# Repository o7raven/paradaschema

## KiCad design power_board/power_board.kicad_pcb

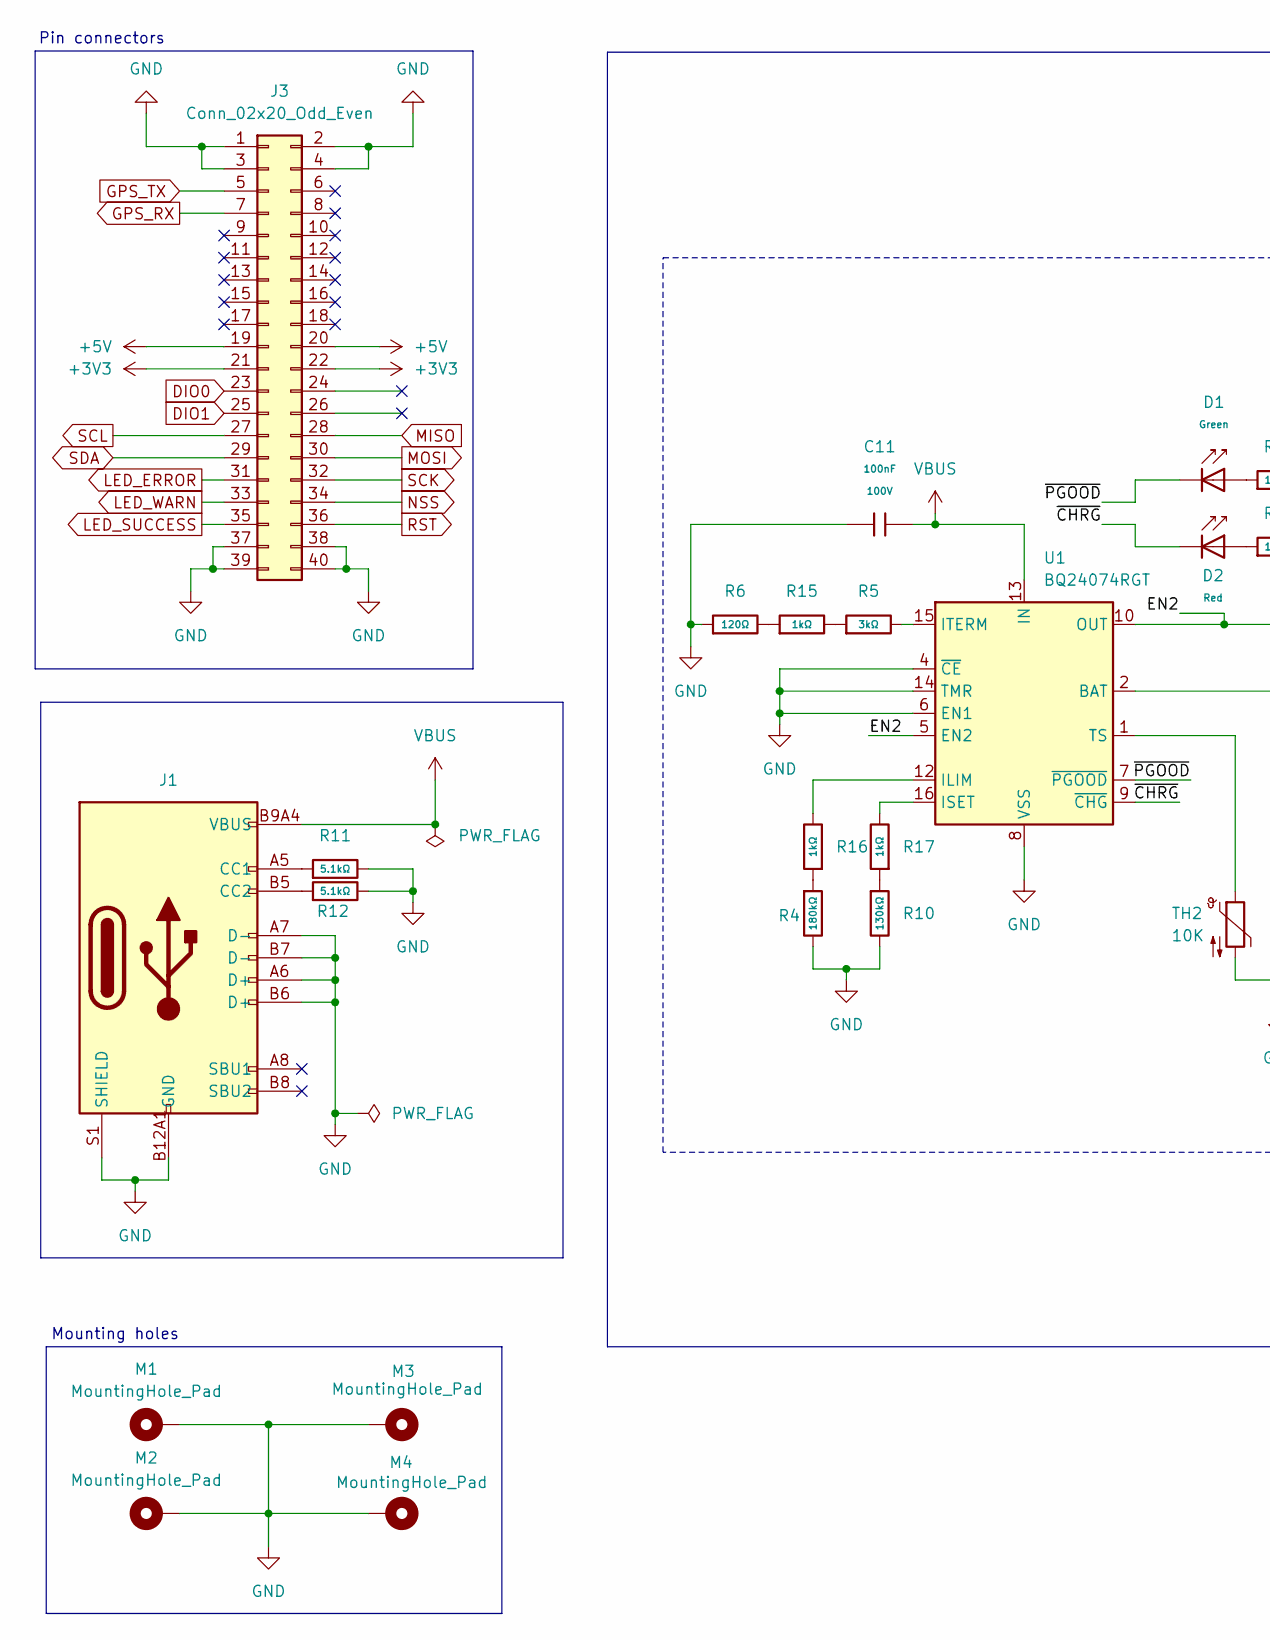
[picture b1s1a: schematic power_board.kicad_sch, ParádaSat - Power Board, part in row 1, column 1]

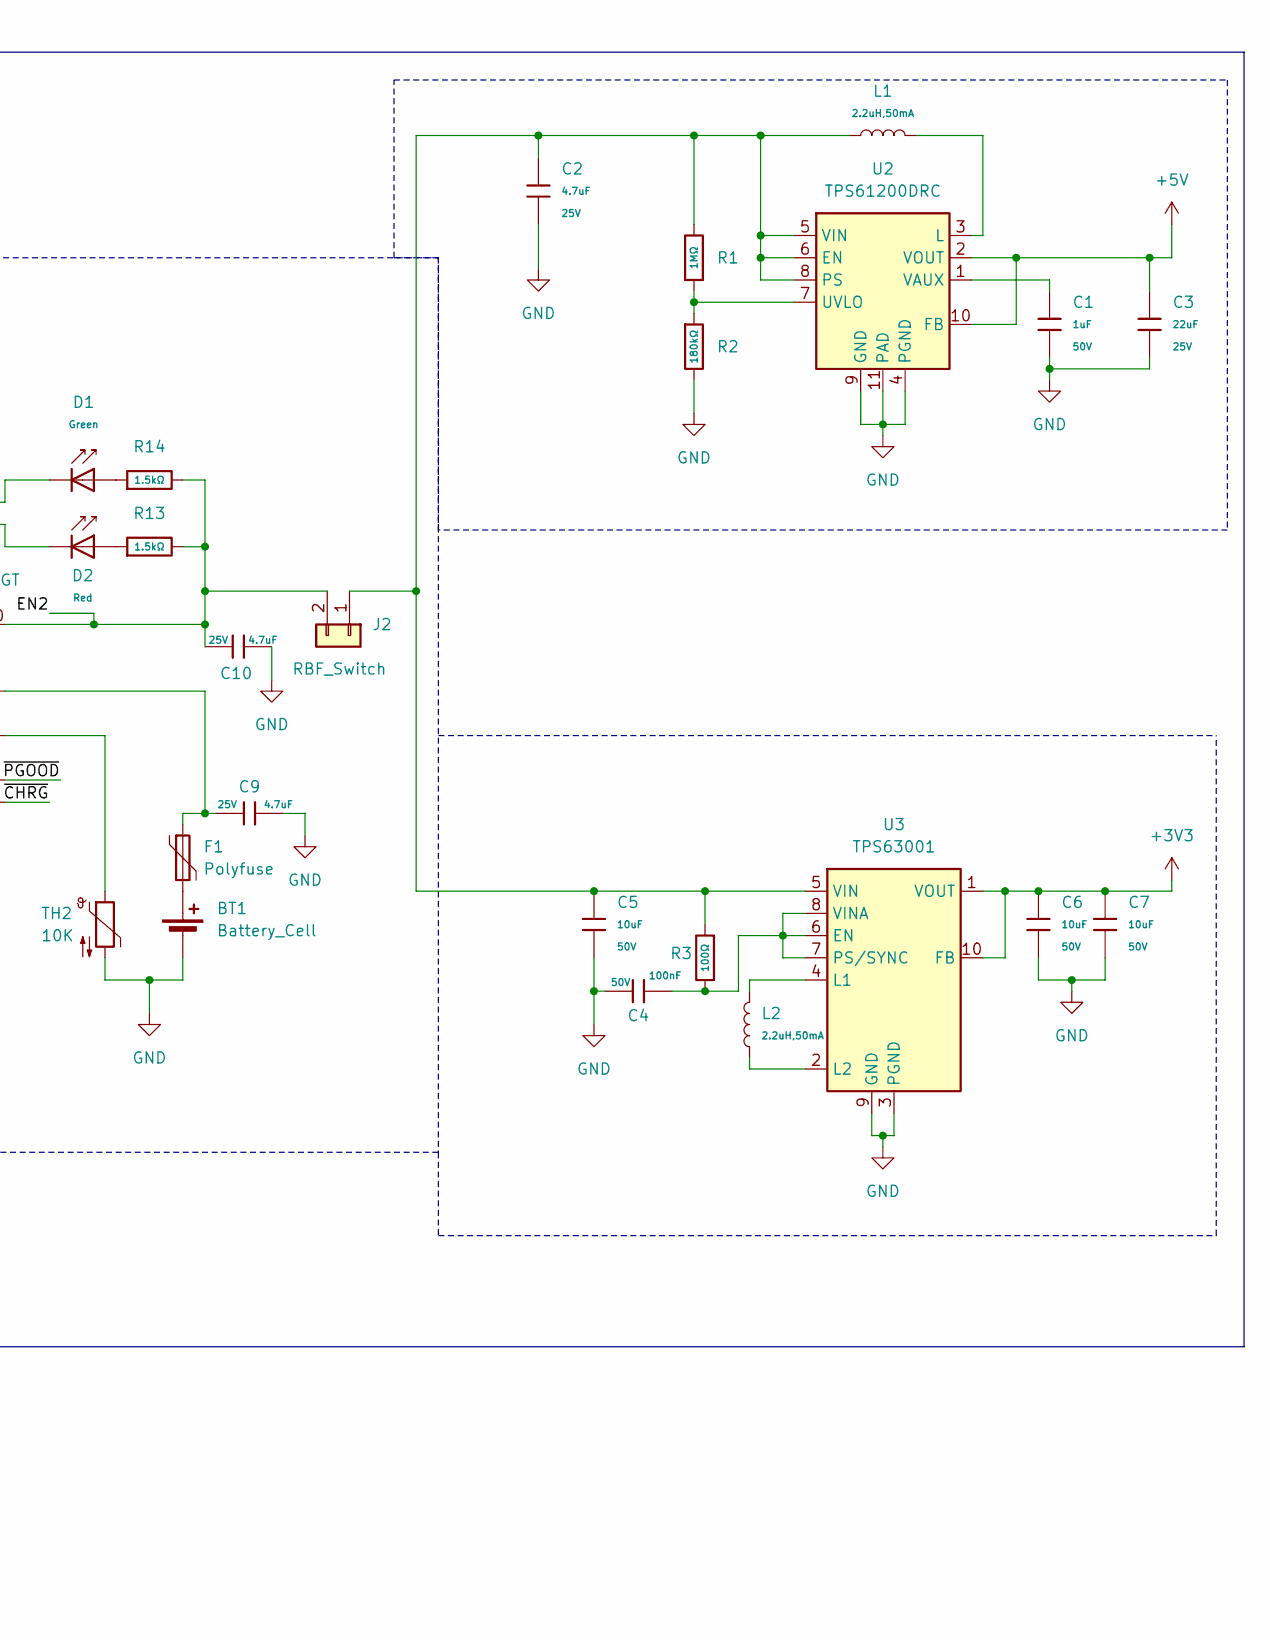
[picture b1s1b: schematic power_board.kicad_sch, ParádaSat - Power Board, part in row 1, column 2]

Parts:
BT1: Battery_Cell; BatteryHolder_MPD_BH-18650-PC
C1: 1uF; C_0805; Voltage Rated 50V; Tolerance ±10%; Part CL21B105KBFNNNE; LCSC C28323
C2, C9, C10: 4.7uF; C_0805; Voltage Rated 25V; Tolerance ±10%; Part CL21A475KAQNNNE; LCSC C1779
C3: 22uF; C_0805; Voltage Rated 25V; Tolerance ±20%; Part CL21A226MAQNNNE; LCSC C45783
C4: 100nF; C_1206; Voltage Rated 50V; Tolerance ±10%; Part CL31B104KBCNNNC; LCSC C24497
C5, C6, C7: 10uF; C_1206; Voltage Rated 50V; Tolerance ±10%; Part CL31A106KBHNNNE; LCSC C13585
C11: 100nF; C_0805; Voltage Rated 100V; Tolerance ±10%; Part CL21B104KCFNNNE; LCSC C28233
D1: Green; D_0805; Part KT-0805G; LCSC C2297
D2: Red; D_0805; Forward Voltage (VF) 1.6V~2.6V; Part NCD0805R1; LCSC C84256
F1: Polyfuse; Fuse_1812_4532Metric_Pad1.30x3.40mm_HandSolder
J1: Connector, USB-TYPE-C-16P; TYPE-C-SMD_HX-TYPE-C-16PIN; LCSC C2927039
J2: RBF_Switch; PhoenixContact_MSTBA_2,5_2-G_1x02_P5.00mm_Horizontal
J3: Conn_02x20_Odd_Even; PinSocket_2x20_P2.54mm_Vertical
L1, L2: 2.2uH,50mA; L_0805; Tolerance ±10%; Part CMI201209U2R2KT; LCSC C1043
M1, M2, M3, M4: MountingHole_Pad; MountingHole_3.2mm_M3_DIN965_Pad
R1: 1MΩ; R_0805; Overload Voltage (Max) 150V; Tolerance ±1%; Part 0805W8F1004T5E; LCSC C17514
R2: 180kΩ; R_0805; Overload Voltage (Max) 150V; Tolerance ±1%; Part 0805W8F1803T5E; LCSC C17501
R3: 100Ω; R_1206; Overload Voltage (Max) 200V; Tolerance ±1%; Part 1206W4F1000T5E; LCSC C17901
R4: 180kΩ; R_0603; Overload Voltage (Max) 75V; Tolerance ±1%; Part 0603WAF1803T5E; LCSC C22827
R5: 3kΩ; R_0603; Overload Voltage (Max) 75V; Tolerance ±1%; Part 0603WAF3001T5E; LCSC C4211
R6: 120Ω; R_1206; Overload Voltage (Max) 200V; Tolerance ±1%; Part 1206W4F1200T5E; LCSC C17909
R10: 130kΩ; R_0603; Overload Voltage (Max) 75V; Tolerance ±1%; Part 0603WAF1303T5E; LCSC C22795
R11, R12: 5.1kΩ; R_0603; Overload Voltage (Max) 75V; Tolerance ±1%; Part 0603WAF5101T5E; LCSC C23186
R13, R14: 1.5kΩ; R_0805; Overload Voltage (Max) 150V; Tolerance ±1%; Part 0805W8F1501T5E; LCSC C4310
R15, R16, R17: 1kΩ; R_0603; Overload Voltage (Max) 75V; Tolerance ±1%; Part 0603WAF1001T5E; LCSC C21190
TH2: 10K; R_Axial_DIN0204_L3.6mm_D1.6mm_P2.54mm_Vertical
U1: BQ24074RGT; VQFN-16-1EP_3x3mm_P0.5mm_EP1.6x1.6mm
U2: TPS61200DRC; Texas_S-PVSON-N10_ThermalVias
U3: TPS63001; Texas_DRC0010J_ThermalVias

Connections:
+3V3: C6.1, C7.1, J3.21, J3.22, U3.1 (VOUT), U3.10 (FB)
+5V: C3.1, J3.19, J3.20, U2.2 (VOUT), U2.10 (FB)
/EN2: C10.1, J2.2, R13.2, R14.2, U1.5 (EN2), U1.10 (OUT), U1.11 (OUT)
/~CHRG: D2.1, U1.9 (~CHG)
/~PGOOD: D1.1, U1.7 (~PGOOD)
DIO0: J3.23
DIO1: J3.25
GND: BT1.2 (-), C1.2, C2.2, C3.2, C4.1, C5.2, C6.2, C7.2, C9.2, C10.2, C11.1, J1.A6 (D+), J1.A7 (D-), J1.A12B1 (GND), J1.B6 (D+), J1.B7 (D-), J1.B12A1 (GND), J1.S1 (SHIELD), J3.1, J3.2, J3.3, J3.4, J3.37, J3.38, J3.39, J3.40, M1.1 (1_1), M2.1 (1_1), M3.1 (1_1), M4.1 (1_1), R2.2, R4.2, R6.1, R10.2, R11.2, R12.2, TH2.2, U1.4 (~CE), U1.6 (EN1), U1.8 (VSS), U1.14 (TMR), U1.17 (VSS), U2.4 (PGND), U2.9 (GND), U2.11 (PAD), U3.3 (PGND), U3.9 (GND), U3.11 (PGND)
GPS_RX: J3.7
GPS_TX: J3.5
LED_ERROR: J3.31
LED_SUCCESS: J3.35
LED_WARN: J3.33
MISO: J3.28
MOSI: J3.30
NSS: J3.34
unnamed: BT1.1 (+), F1.2
unnamed: C9.1, F1.1, U1.2 (BAT), U1.3 (BAT)
unnamed: D1.2, R14.1
unnamed: D2.2, R13.1
unnamed: J1.A5 (CC1), R11.1
unnamed: J1.B5 (CC2), R12.1
unnamed: C2.1, C5.1, J2.1, L1.1, R1.2, R3.2, U2.5 (VIN), U2.6 (EN), U2.8 (PS), U3.5 (VIN)
unnamed: R10.1, R17.1
unnamed: R6.2, R15.1
unnamed: R5.1, R15.2
unnamed: R4.1, R16.1
unnamed: R16.2, U1.12 (ILIM)
unnamed: R17.2, U1.16 (ISET)
unnamed: R5.2, U1.15 (ITERM)
unnamed: TH2.1, U1.1 (TS)
unnamed: L1.2, U2.3 (L)
unnamed: R1.1, R2.1, U2.7 (UVLO)
unnamed: C1.1, U2.1 (VAUX)
unnamed: C4.2, R3.1, U3.6 (EN), U3.7 (PS/SYNC), U3.8 (VINA)
unnamed: L2.2, U3.4 (L1)
unnamed: L2.1, U3.2 (L2)
RST: J3.36
SCK: J3.32
SCL: J3.27
SDA: J3.29
VBUS: C11.2, J1.A9B4 (VBUS), J1.B9A4 (VBUS), U1.13 (IN)

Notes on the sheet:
Mounting holes
Pin connectors

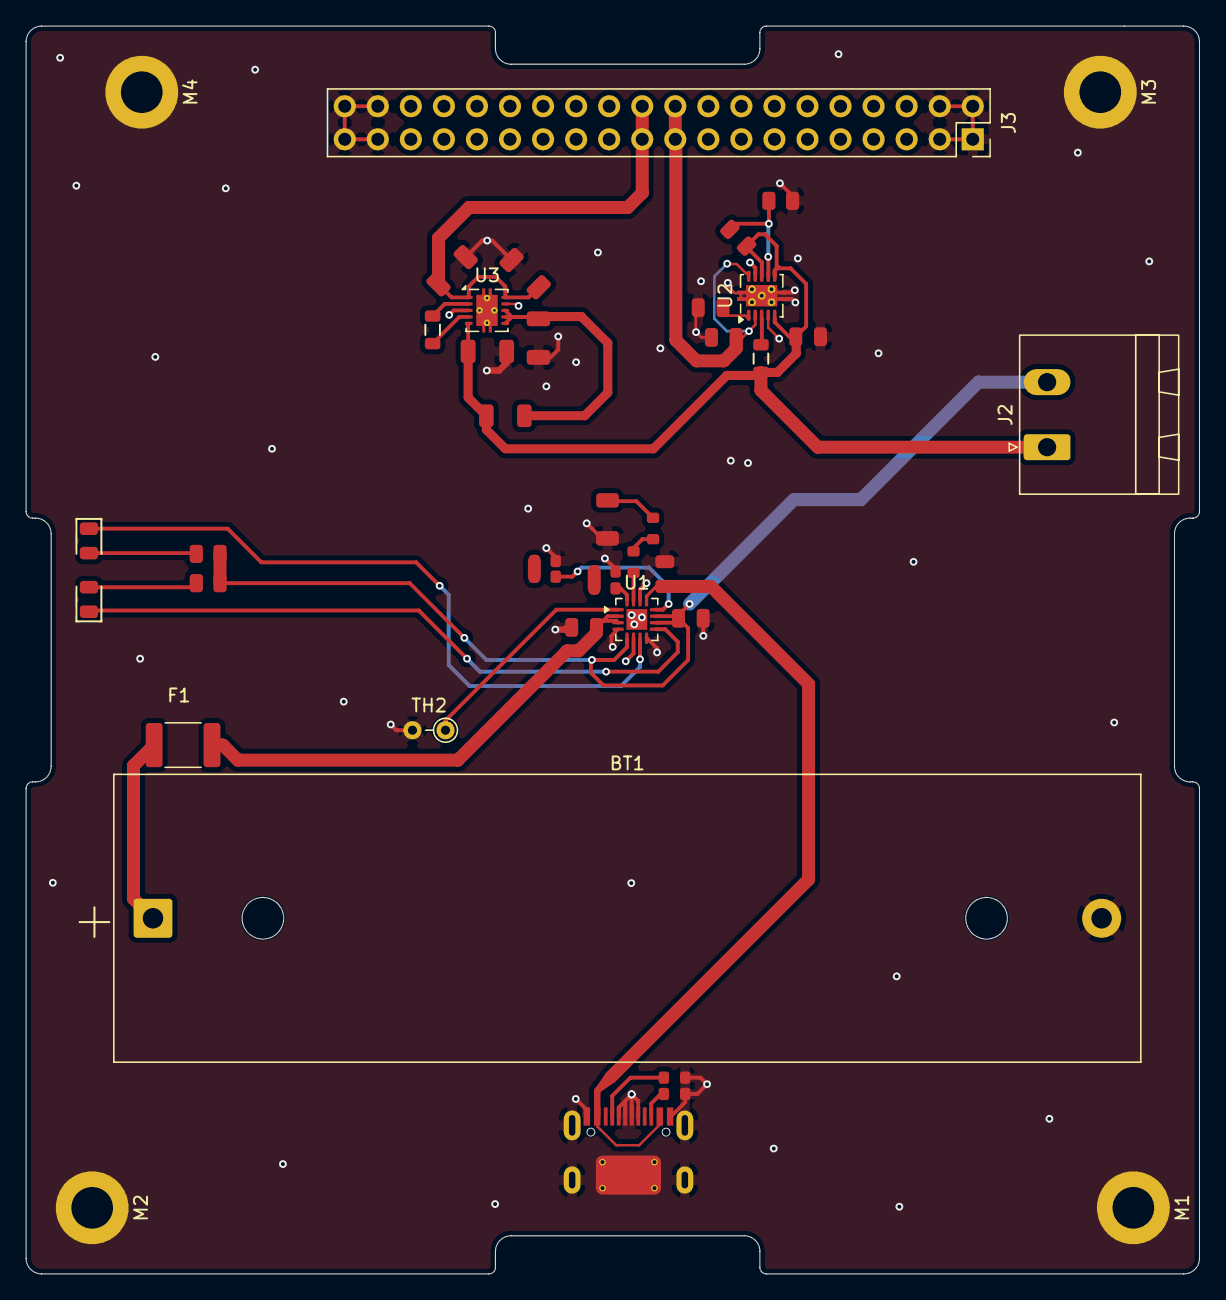
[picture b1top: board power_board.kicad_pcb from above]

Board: 2 copper layers, 90.2 x 95.9 mm, 41 parts (0 on the bottom side), 28 nets.

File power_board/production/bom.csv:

Designator,Footprint,Quantity,Value,LCSC Part #
BT1,BatteryHolder_MPD_BH-18650-PC,1,Battery_Cell,
C1,C_0805,1,1uF,C28323
"C10, C2, C9",C_0805,3,4.7uF,C1779
C11,C_0805,1,100nF,C28233
C3,C_0805,1,22uF,C45783
C4,C_1206,1,100nF,C24497
"C5, C6, C7",C_1206,3,10uF,C13585
D1,D_0805,1,Green,C2297
D2,D_0805,1,Red,C84256
F1,1812,1,Polyfuse,
J1,TYPE-C-SMD_HX-TYPE-C-16PIN,1,"Connector, USB-TYPE-C-16P",C2927039
J2,"PhoenixContact_MSTBA_2,5_2-G_1x02_P5.00mm_Horizontal",1,RBF_Switch,
J3,PinSocket_2x20_P2.54mm_Vertical,1,Conn_02x20_Odd_Even,
"L1, L2",L_0805,2,"2.2uH,50mA",C1043
R1,R_0805,1,1MΩ,C17514
R10,R_0603,1,130kΩ,C22795
"R11, R12",R_0603,2,5.1kΩ,C23186
"R13, R14",R_0805,2,1.5kΩ,C4310
"R15, R16, R17",R_0603,3,1kΩ,C21190
R2,R_0805,1,180kΩ,C17501
R3,R_1206,1,100Ω,C17901
R4,R_0603,1,180kΩ,C22827
R5,R_0603,1,3kΩ,C4211
R6,R_1206,1,120Ω,C17909
TH2,R_Axial_DIN0204_L3.6mm_D1.6mm_P2.54mm_Vertical,1,10K,
U1,VQFN-16-1EP_3x3mm_P0.5mm_EP1.6x1.6mm,1,BQ24074RGT,
U2,Texas_S-PVSON-N10_ThermalVias,1,TPS61200DRC,
U3,Texas_DRC0010J_ThermalVias,1,TPS63001,

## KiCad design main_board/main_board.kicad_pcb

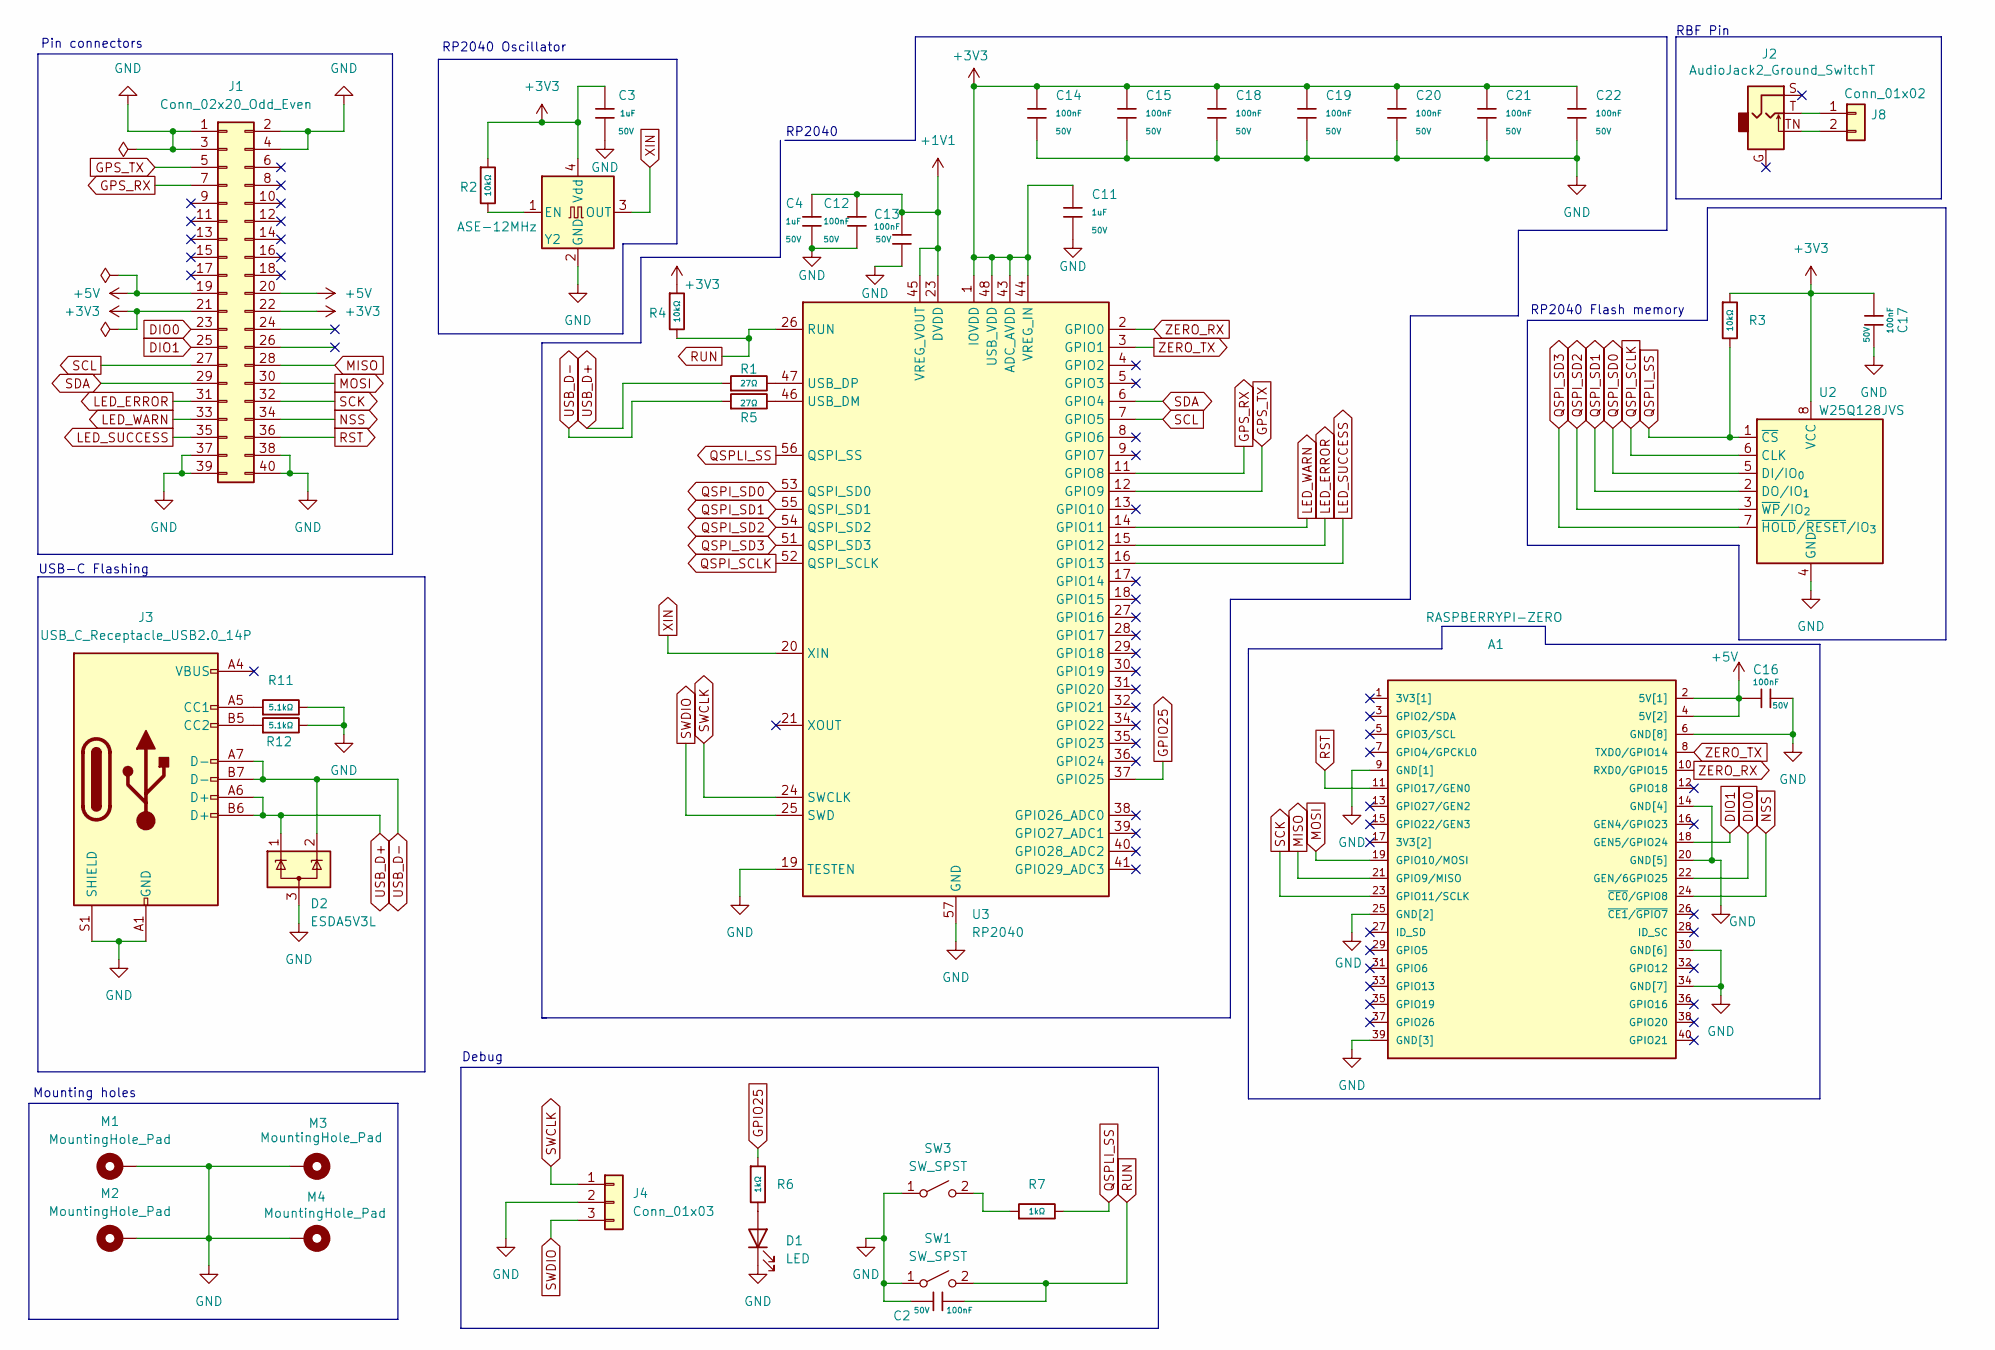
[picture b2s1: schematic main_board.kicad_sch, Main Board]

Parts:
A1: RASPBERRYPI-ZERO; RASPBERRYPI-ZERO_RPI-ZERO
C2, C12, C13, C14, C15, C16, C17, C18, C19, C20, C21, C22: 100nF; C_0603; Voltage Rated 50V; Tolerance ±10%; Part CC0603KRX7R9BB104; LCSC C14663
C3, C4, C11: 1uF; C_0603; Voltage Rated 50V; Tolerance ±10%; Part CL10A105KB8NNNC; LCSC C15849
D1: LED; LED_0402_1005Metric
D2: ESDA5V3L; SOT-23-3
J1: Conn_02x20_Odd_Even; PinSocket_2x20_P2.54mm_Vertical
J2: AudioJack2_Ground_SwitchT; Jack_3.5mm_CUI_SJ1-3524N_Horizontal
J3: USB_C_Receptacle_USB2.0_14P; USB_C_Receptacle_GCT_USB4085
J4: Conn_01x03; JST_XH_S3B-XH-A-1_1x03_P2.50mm_Horizontal
J8: Conn_01x02; JST_XH_S2B-XH-A_1x02_P2.50mm_Horizontal
M1, M2, M3, M4: MountingHole_Pad; MountingHole_3.2mm_M3_DIN965_Pad
R1, R5: 27Ω; R_0603; Overload Voltage (Max) 75V; Tolerance ±1%; Part 0603WAF270JT5E; LCSC C25190
R2, R3, R4: 10kΩ; R_0603; Overload Voltage (Max) 75V; Tolerance ±1%; Part 0603WAF1002T5E; LCSC C25804
R6, R7: 1kΩ; R_0603; Overload Voltage (Max) 75V; Tolerance ±1%; Part 0603WAF1001T5E; LCSC C21190
R11, R12: 5.1kΩ; R_0603; Overload Voltage (Max) 75V; Tolerance ±1%; Part 0603WAF5101T5E; LCSC C23186
SW1, SW3: SW_SPST; SW_SPST_B3S-1000
U2: W25Q128JVS; SOIC-8_5.3x5.3mm_P1.27mm
U3: RP2040; QFN-56-1EP_7x7mm_P0.4mm_EP3.2x3.2mm_ThermalVias; LCSC C2040
Y2: ASE-12MHz; Oscillator_SMD_Abracon_ASE-4Pin_3.2x2.5mm

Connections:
+1V1: C4.1, C12.1, C13.1, U3.23 (DVDD), U3.45 (VREG_VOUT), U3.50 (DVDD)
+3V3: C3.1, C11.1, C14.1, C15.1, C17.1, C18.1, C19.1, C20.1, C21.1, C22.1, J1.21, J1.22, R2.1, R3.1, R4.1, U2.8 (VCC), U3.1 (IOVDD), U3.10 (IOVDD), U3.22 (IOVDD), U3.33 (IOVDD), U3.42 (IOVDD), U3.43 (ADC_AVDD), U3.44 (VREG_IN), U3.48 (USB_VDD), U3.49 (IOVDD), Y2.4 (Vdd)
+5V: A1.2 (5V[1]), A1.4 (5V[2]), C16.1, J1.19, J1.20
DIO0: A1.22 (GEN/6GPIO25), J1.23
DIO1: A1.18 (GEN5/GPIO24), J1.25
GND: A1.6 (GND[8]), A1.9 (GND[1]), A1.14 (GND[4]), A1.20 (GND[5]), A1.25 (GND[2]), A1.30 (GND[6]), A1.34 (GND[7]), A1.39 (GND[3]), C2.1, C3.2, C4.2, C11.2, C12.2, C13.2, C14.2, C15.2, C16.2, C17.2, C18.2, C19.2, C20.2, C21.2, C22.2, D1.1 (K), D2.3 (A), J1.1, J1.2, J1.3, J1.4, J1.37, J1.38, J1.39, J1.40, J3.A1 (GND), J3.A12 (GND), J3.B1 (GND), J3.B12 (GND), J3.S1 (SHIELD), J4.2, M1.1 (1_1), M2.1 (1_1), M3.1 (1_1), M4.1 (1_1), R11.2, R12.2, SW1.1 (A), SW3.1 (A), U2.4 (GND), U3.19 (TESTEN), U3.57 (GND), Y2.2 (GND)
GPIO25: R6.1, U3.37 (GPIO25)
GPS_RX: J1.7, U3.11 (GPIO8)
GPS_TX: J1.5, U3.12 (GPIO9)
LED_ERROR: J1.31, U3.15 (GPIO12)
LED_SUCCESS: J1.35, U3.16 (GPIO13)
LED_WARN: J1.33, U3.14 (GPIO11)
MISO: A1.21 (GPIO9/MISO), J1.28
MOSI: A1.19 (GPIO10/MOSI), J1.30
NSS: A1.24 (~CE0/GPIO8), J1.34
unnamed: D1.2 (A), R6.2
unnamed: J3.A5 (CC1), R11.1
unnamed: J3.B5 (CC2), R12.1
unnamed: J2.T, J8.1
unnamed: J2.TN, J8.2
unnamed: R7.1, SW3.2 (B)
unnamed: R5.2, U3.46 (USB_DM)
unnamed: R1.2, U3.47 (USB_DP)
unnamed: R2.2, Y2.1 (EN)
QSPI_SCLK: U2.6 (CLK), U3.52 (QSPI_SCLK)
QSPI_SD0: U2.5 (DI/IO_{0}), U3.53 (QSPI_SD0)
QSPI_SD1: U2.2 (DO/IO_{1}), U3.55 (QSPI_SD1)
QSPI_SD2: U2.3 (~WP/IO_{2}), U3.54 (QSPI_SD2)
QSPI_SD3: U2.7 (~HOLD/~RESET/IO_{3}), U3.51 (QSPI_SD3)
QSPLI_SS: R3.2, R7.2, U2.1 (~CS), U3.56 (QSPI_SS)
RST: A1.11 (GPIO17/GEN0), J1.36
RUN: C2.2, R4.2, SW1.2 (B), U3.26 (RUN)
SCK: A1.23 (GPIO11/SCLK), J1.32
SCL: J1.27, U3.7 (GPIO5)
SDA: J1.29, U3.6 (GPIO4)
SWCLK: J4.1, U3.24 (SWCLK)
SWDIO: J4.3, U3.25 (SWD)
USB_D+: D2.1 (K), J3.A6 (D+), J3.B6 (D+), R1.1
USB_D-: D2.2 (K), J3.A7 (D-), J3.B7 (D-), R5.1
XIN: U3.20 (XIN), Y2.3 (OUT)
ZERO_RX: A1.10 (RXD0/GPIO15), U3.2 (GPIO0)
ZERO_TX: A1.8 (TXD0/GPIO14), U3.3 (GPIO1)

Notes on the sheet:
RP2040 Oscillator
Debug
Pin connectors
Mounting holes
RBF Pin
RP2040
RP2040 Flash memory
USB-C Flashing

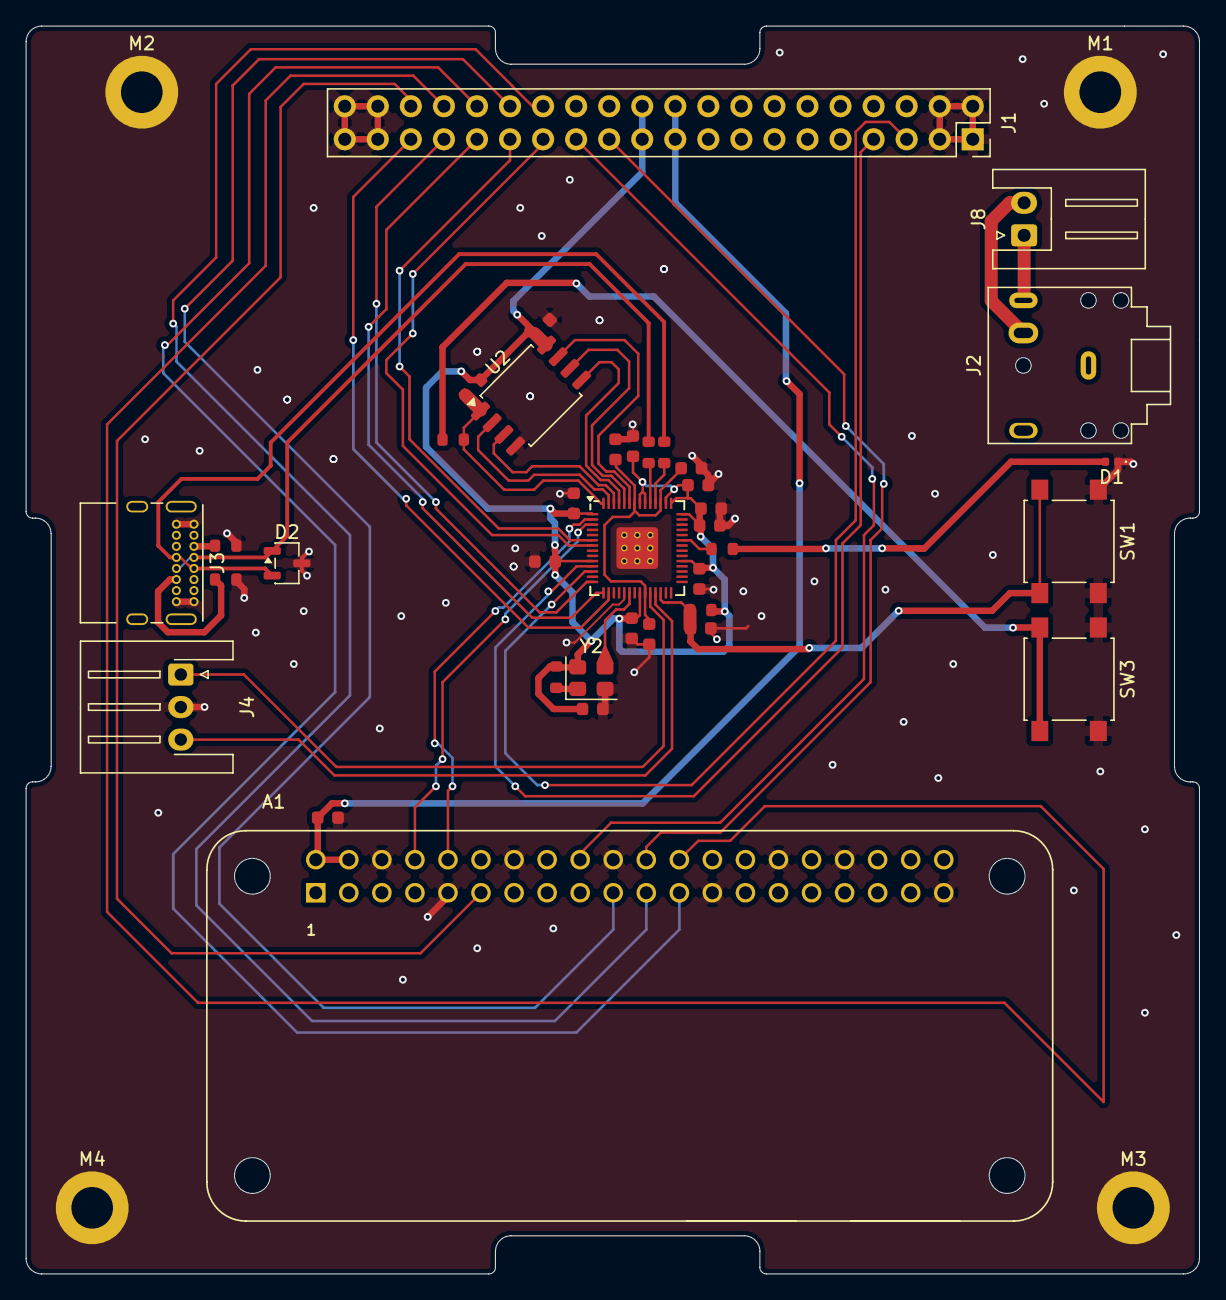
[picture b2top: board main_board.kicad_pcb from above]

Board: 2 copper layers, 90.2 x 95.9 mm, 41 parts (0 on the bottom side), 42 nets.

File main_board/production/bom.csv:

Designator,Footprint,Quantity,Value,LCSC Part #
A1,RASPBERRYPI-ZERO_RPI-ZERO,1,RASPBERRYPI-ZERO,
"C11, C3, C4",C_0603,3,1uF,C15849
"C12, C13, C14, C15, C16, C17, C18, C19, C2, C20, C21, C22",C_0603,12,100nF,C14663
D1,0402,1,LED,
D2,SOT-23-3,1,ESDA5V3L,
J1,PinSocket_2x20_P2.54mm_Vertical,1,Conn_02x20_Odd_Even,
J2,Jack_3.5mm_CUI_SJ1-3524N_Horizontal,1,AudioJack2_Ground_SwitchT,
J3,USB_C_Receptacle_GCT_USB4085,1,USB_C_Receptacle_USB2.0_14P,
J4,JST_XH_S3B-XH-A-1_1x03_P2.50mm_Horizontal,1,Conn_01x03,
J8,JST_XH_S2B-XH-A_1x02_P2.50mm_Horizontal,1,Conn_01x02,
"R1, R5",R_0603,2,27Ω,C25190
"R11, R12",R_0603,2,5.1kΩ,C23186
"R2, R3, R4",R_0603,3,10kΩ,C25804
"R6, R7",R_0603,2,1kΩ,C21190
"SW1, SW3",SW_SPST_B3S-1000,2,SW_SPST,
U2,SOIC-8_5.3x5.3mm_P1.27mm,1,W25Q128JVS,
U3,QFN-56-1EP_7x7mm_P0.4mm_EP3.2x3.2mm_ThermalVias,1,RP2040,C2040
Y2,Oscillator_SMD_Abracon_ASE-4Pin_3.2x2.5mm,1,ASE-12MHz,

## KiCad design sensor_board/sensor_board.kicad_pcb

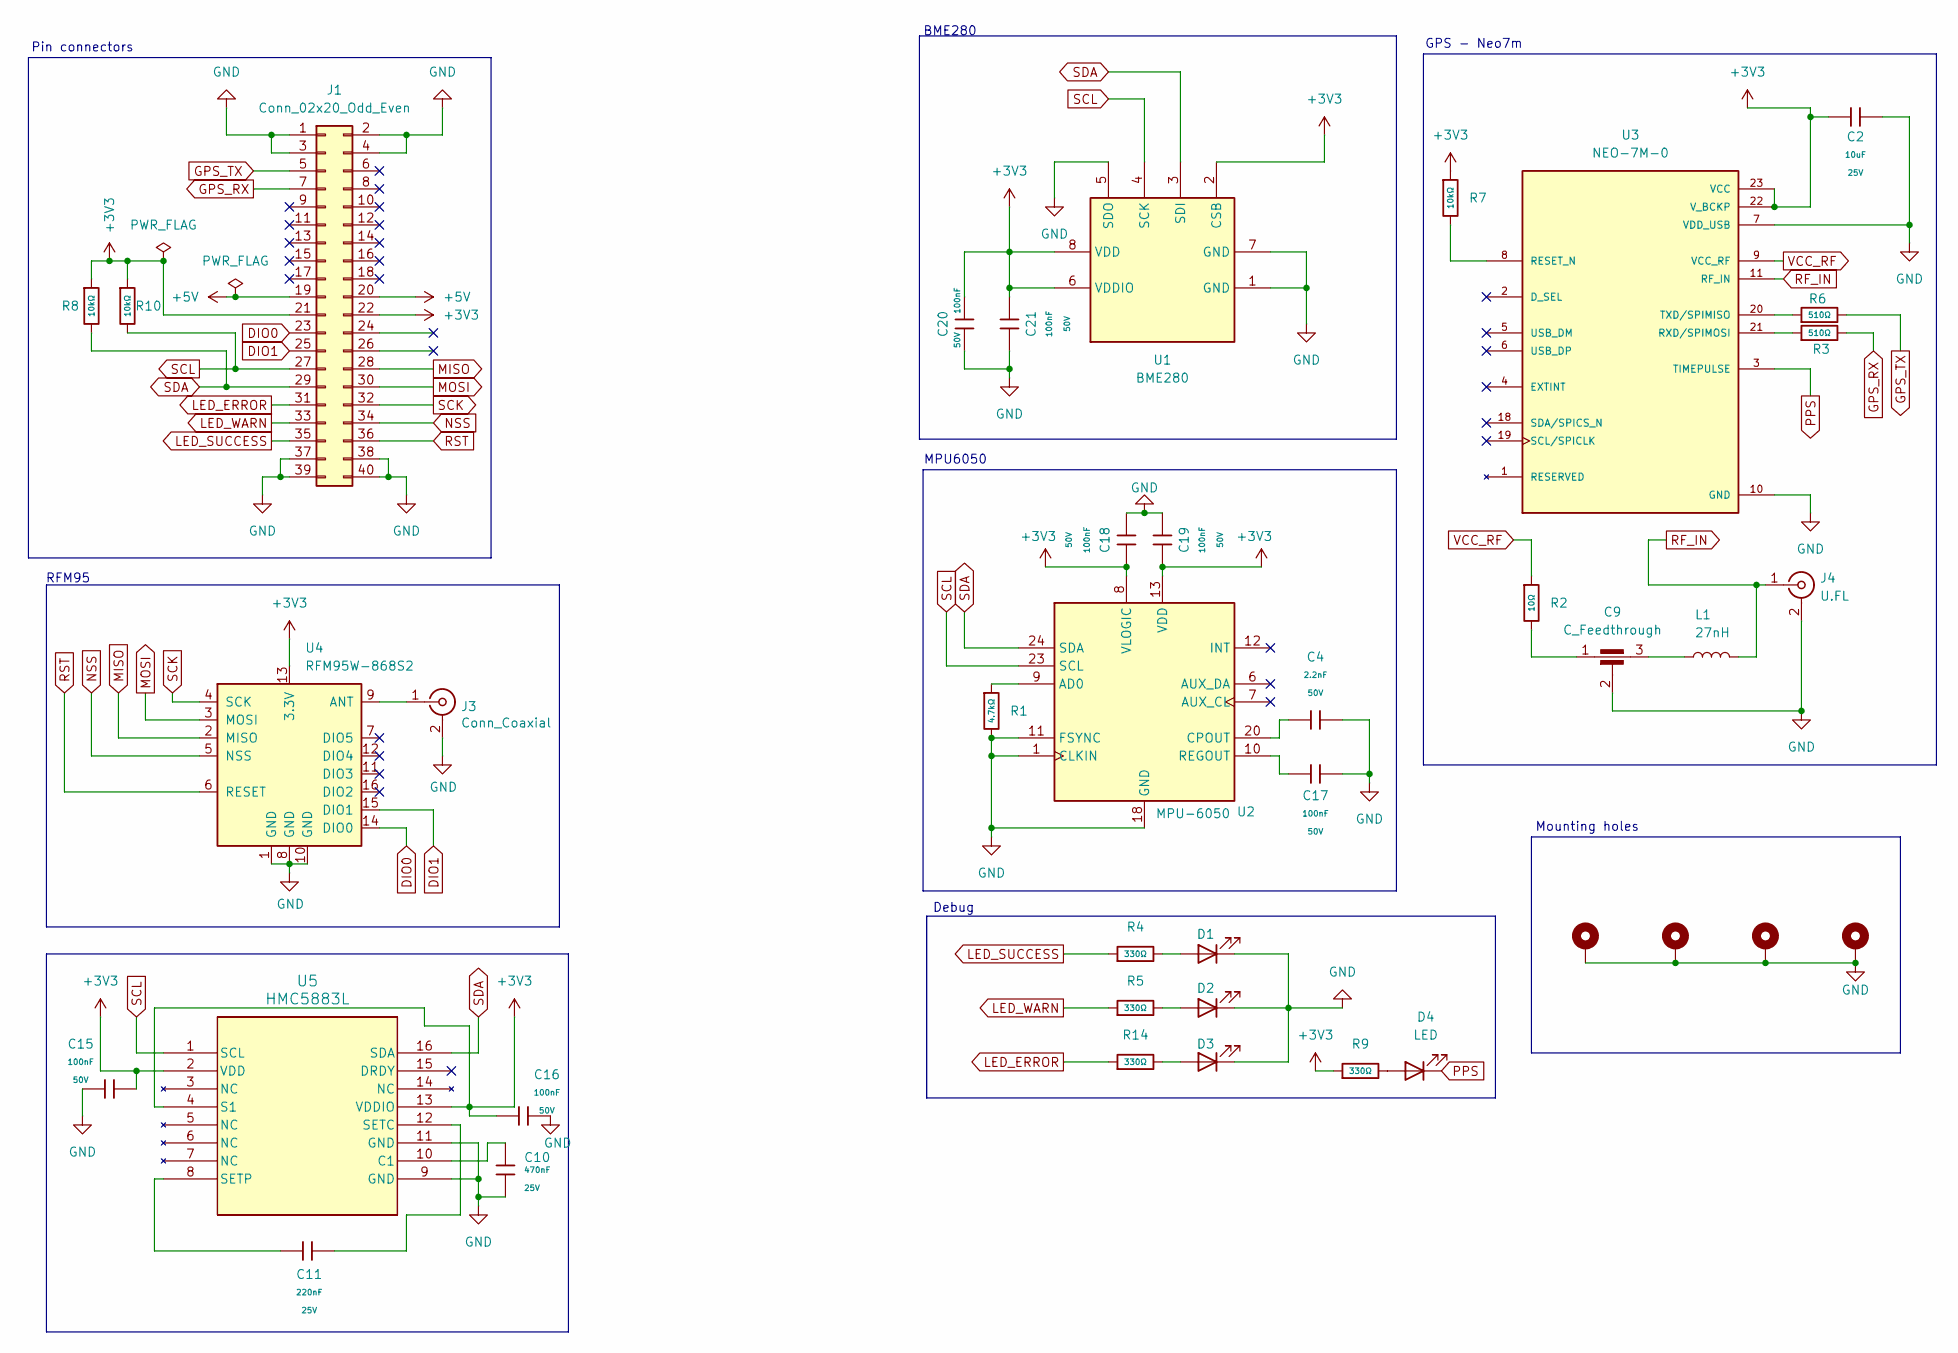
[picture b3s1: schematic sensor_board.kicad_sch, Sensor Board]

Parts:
C2: 10uF; C_0603; Voltage Rated 25V; Tolerance ±20%; Part CL10A106MA8NRNC; LCSC C96446
C4: 2.2nF; C_0603; Voltage Rated 50V; Tolerance ±10%; Part 0603B222K500NT; LCSC C1604
C9: C_Feedthrough; Filter_Mini-Circuits_FV1206-7
C10: 470nF; C_0603; Voltage Rated 25V; Tolerance ±10%; Part CL10B474KA8NNNC; LCSC C1623
C11: 220nF; C_0603; Voltage Rated 25V; Tolerance ±10%; Part CL10B224KA8NNNC; LCSC C21120
C15, C16, C17, C18, C19, C20, C21: 100nF; C_0603; Voltage Rated 50V; Tolerance ±10%; Part CC0603KRX7R9BB104; LCSC C14663
D1, D2, D3, D4: LED; LED_D8.0mm
J1: Conn_02x20_Odd_Even; PinSocket_2x20_P2.54mm_Vertical
J3: Conn_Coaxial; SMA_Amphenol_132134-11_Vertical
J4: U.FL; IPEX-SMD_BWIPX-1-001E; LCSC C5137195
L1: 27nH; L_0603_1608Metric
M1, M2, M3, M4: HOLE; MountingHole_3.2mm_M3_DIN965_Pad
R1: 4.7kΩ; R_0603; Overload Voltage (Max) 75V; Tolerance ±1%; Part 0603WAF4701T5E; LCSC C23162
R2: 10Ω; R_0603; Overload Voltage (Max) 75V; Tolerance ±1%; Part 0603WAF100JT5E; LCSC C22859
R3, R6: 510Ω; R_0603; Overload Voltage (Max) 75V; Tolerance ±1%; Part 0603WAF5100T5E; LCSC C23193
R4, R5, R9, R14: 330Ω; R_0603; Overload Voltage (Max) 75V; Tolerance ±1%; Part 0603WAF3300T5E; LCSC C23138
R7, R8, R10: 10kΩ; R_0603; Overload Voltage (Max) 75V; Tolerance ±1%; Part 0603WAF1002T5E; LCSC C25804
U1: BME280; Bosch_LGA-8_2.5x2.5mm_P0.65mm_ClockwisePinNumbering
U2: MPU-6050; InvenSense_QFN-24_4x4mm_P0.5mm
U3: NEO-7M-0; XCVR_NEO-7M-0; PARTREV R10
U4: RFM95W-868S2; HOPERF_RFM9XW_SMD
U5: HMC5883L; LPCC16_HNW

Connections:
+3V3: C2.1, C15.2, C16.1, C18.2, C19.1, C20.1, C21.2, J1.21, J1.22, R7.1, R8.1, R9.1, R10.1, U1.2 (CSB), U1.6 (VDDIO), U1.8 (VDD), U2.8 (VLOGIC), U2.13 (VDD), U3.22 (V_BCKP), U3.23 (VCC), U4.13 (3.3V), U5.2 (VDD), U5.4 (S1), U5.13 (VDDIO)
+5V: J1.19, J1.20
DIO0: J1.23, U4.14 (DIO0)
DIO1: J1.25, U4.15 (DIO1)
GND: C2.2, C4.2, C9.2, C10.2, C15.1, C16.2, C17.2, C18.1, C19.2, C20.2, C21.1, D1.1 (K), D2.1 (K), D3.1 (K), J1.1, J1.2, J1.3, J1.4, J1.37, J1.38, J1.39, J1.40, J3.2 (Ext), J4.2 (Ext), M1.1, M2.1, M3.1, M4.1, R1.2, U1.1 (GND), U1.5 (SDO), U1.7 (GND), U2.1 (CLKIN), U2.11 (FSYNC), U2.18 (GND), U3.7 (VDD_USB), U3.10 (GND), U3.12 (GND), U3.13 (GND), U3.24 (GND), U4.1 (GND), U4.8 (GND), U4.10 (GND), U5.9 (GND), U5.11 (GND)
GPS_RX: J1.7, R3.2
GPS_TX: J1.5, R6.2
LED_ERROR: J1.31, R14.1
LED_SUCCESS: J1.35, R4.1
LED_WARN: J1.33, R5.1
MISO: J1.28, U4.2 (MISO)
MOSI: J1.30, U4.3 (MOSI)
NSS: J1.34, U4.5 (NSS)
unnamed: C9.1, R2.2
unnamed: C9.3, L1.1
unnamed: D1.2 (A), R4.2
unnamed: D2.2 (A), R5.2
unnamed: D3.2 (A), R14.2
unnamed: D4.2 (A), R9.2
unnamed: J3.1 (In), U4.9 (ANT)
unnamed: R1.1, U2.9 (AD0)
unnamed: C4.1, U2.20 (CPOUT)
unnamed: C17.1, U2.10 (REGOUT)
unnamed: R7.2, U3.8 (RESET_N)
unnamed: R3.1, U3.21 (RXD/SPIMOSI)
unnamed: R6.1, U3.20 (TXD/SPIMISO)
unnamed: C10.1, U5.10 (C1)
unnamed: C11.1, U5.12 (SETC)
unnamed: C11.2, U5.8 (SETP)
PPS: D4.1 (K), U3.3 (TIMEPULSE)
RF_IN: J4.1 (In), L1.2, U3.11 (RF_IN)
RST: J1.36, U4.6 (RESET)
SCK: J1.32, U4.4 (SCK)
SCL: J1.27, R10.2, U1.4 (SCK), U2.23 (SCL), U5.1 (SCL)
SDA: J1.29, R8.2, U1.3 (SDI), U2.24 (SDA), U5.16 (SDA)
VCC_RF: R2.1, U3.9 (VCC_RF)

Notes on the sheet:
Mounting holes
MPU6050
BME280
RFM95
Debug
GPS - Neo7m
Pin connectors

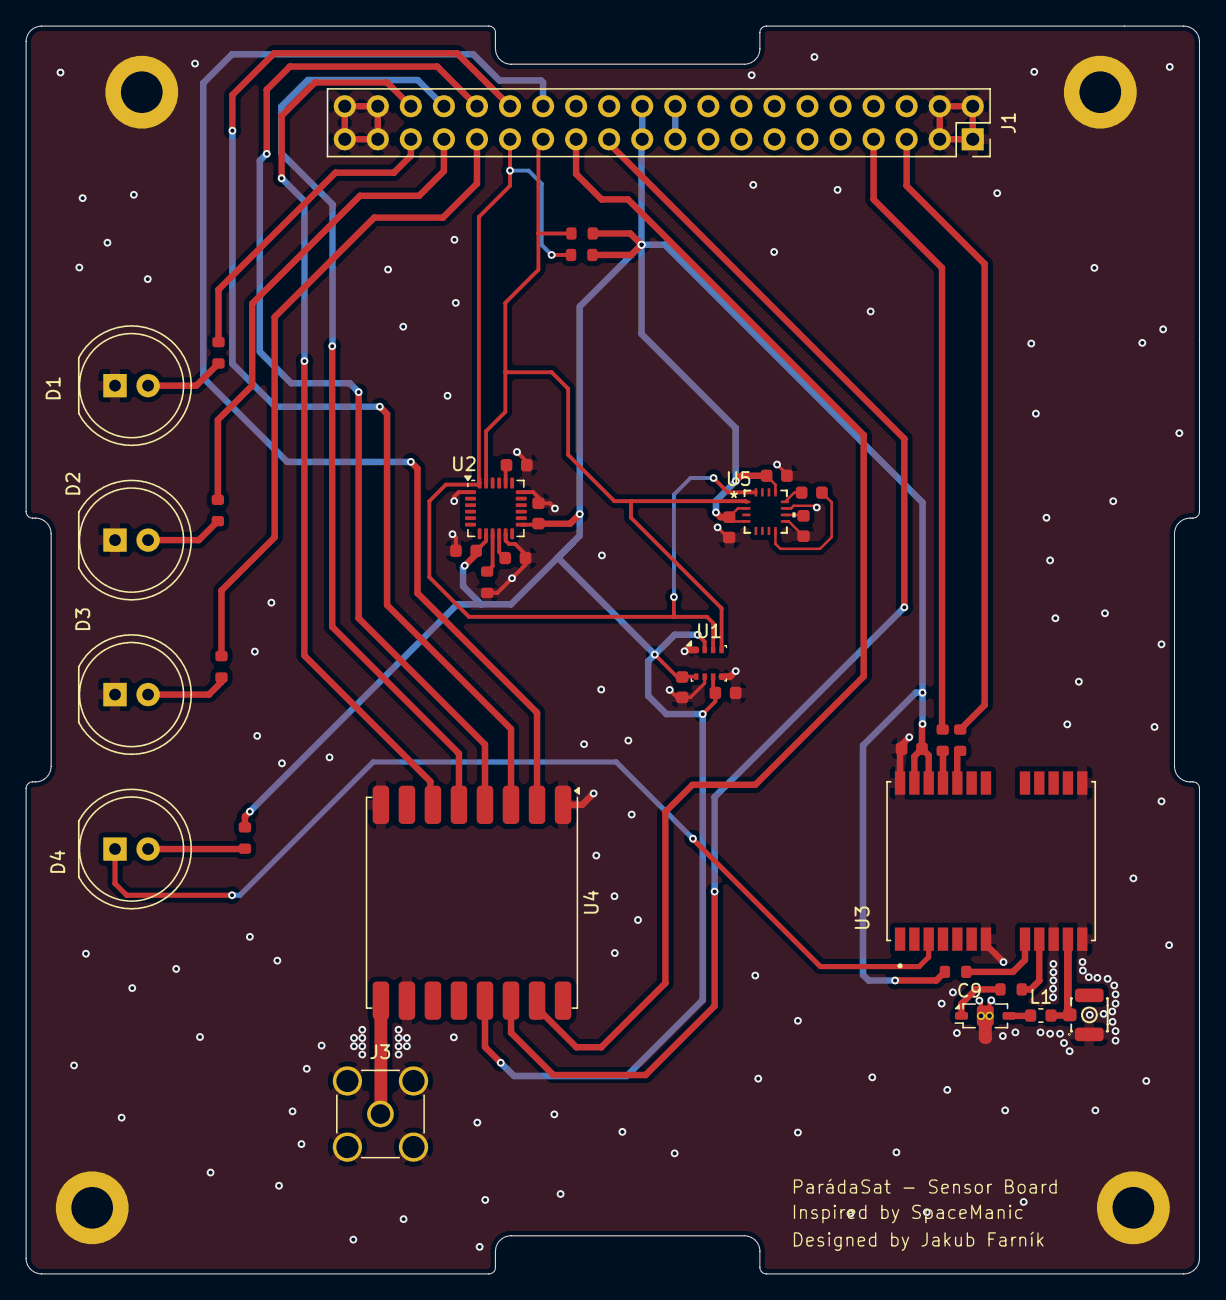
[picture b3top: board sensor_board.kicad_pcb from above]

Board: 2 copper layers, 90.2 x 95.9 mm, 40 parts (0 on the bottom side), 36 nets.

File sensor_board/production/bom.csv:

Designator,Footprint,Quantity,Value,LCSC Part #
C10,C_0603,1,470nF,C1623
C11,C_0603,1,220nF,C21120
"C15, C16, C17, C18, C19, C20, C21",C_0603,7,100nF,C14663
C2,C_0603,1,10uF,C96446
C4,C_0603,1,2.2nF,C1604
C9,Filter_Mini-Circuits_FV1206-7,1,C_Feedthrough,
"D1, D2, D3, D4",LED_D8.0mm,4,LED,
J1,PinSocket_2x20_P2.54mm_Vertical,1,Conn_02x20_Odd_Even,
J3,SMA_Amphenol_132134-11_Vertical,1,Conn_Coaxial,
J4,IPEX-SMD_BWIPX-1-001E,1,U.FL,C5137195
L1,0603,1,27nH,
R1,R_0603,1,4.7kΩ,C23162
"R10, R7, R8",R_0603,3,10kΩ,C25804
"R14, R4, R5, R9",R_0603,4,330Ω,C23138
R2,R_0603,1,10Ω,C22859
"R3, R6",R_0603,2,510Ω,C23193
U1,Bosch_LGA-8_2.5x2.5mm_P0.65mm_ClockwisePinNumbering,1,BME280,
U2,InvenSense_QFN-24_4x4mm_P0.5mm,1,MPU-6050,
U3,XCVR_NEO-7M-0,1,NEO-7M-0,
U4,HOPERF_RFM9XW_SMD,1,RFM95W-868S2,
U5,LPCC16_HNW,1,HMC5883L,

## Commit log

2026-03-18 balbloabla
2026-03-23 sensor board
2026-03-23 sensor
2026-03-25 sdlkfj
2026-03-30 desky
2026-04-10 completed sensor
2026-04-14 main board complete
